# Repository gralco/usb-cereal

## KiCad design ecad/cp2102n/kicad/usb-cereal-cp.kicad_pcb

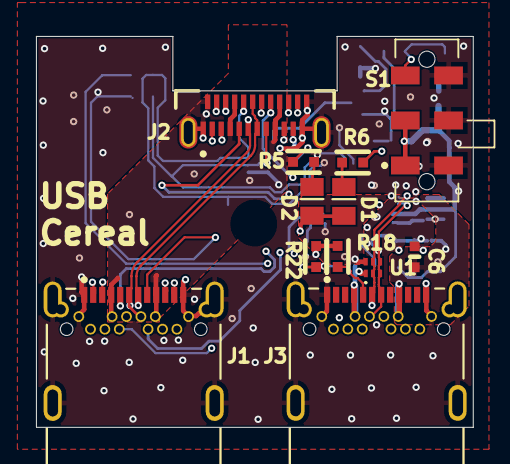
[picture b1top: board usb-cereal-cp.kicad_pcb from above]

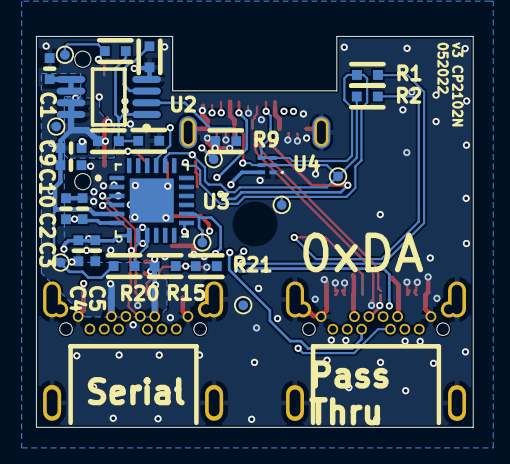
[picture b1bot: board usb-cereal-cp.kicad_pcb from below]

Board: 6 copper layers, 24.3 x 21.7 mm, 40 parts (28 on the bottom side), 35 nets.

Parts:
C1, C9, C10: 1µF; SMD-0402C
C2, C5: 0.10µF; SMD-0402C
C3, C4: 4.7µF; SMD-0402C
C6: 10nF; SMD-0402C
D1: LTST-C171GKT; 0805
D2: LTST-C171KSKT; 0805
J1, J3: UJ31-CH-G1-SMT-TR; CUI_UJ31-CH-G1-SMT-TR
J2: USB4155-03-C_REVA; GCT_USB4155-03-C_REVA
R1, R2, R16: 0.0; SMD-0402-RES
R5: 1k; SMD-0402-RES
R6: 270; SMD-0402-RES
R9, R10: 53.6k; SMD-0402-RES
R11, R15, R20: 22.1k; SMD-0402-RES
R12: 30.1k; SMD-0402-RES
R18, R22: 5.1k; SMD-0402-RES
R21: 47.5k; SMD-0402-RES
S1: JS202011JAQN
TP1, TP3, TP4, TP5, TP6, TP7, TP8, TP9: GND; Testpoint
U1, U4: ESDR0502NMUTAG; ONSC-UDFN-6-517AA-01_V
U2: TPS77401DGK; TI-DGK8_N
U3: CP2102N-A02-GQFN24R; QFN50P400X400X80-25N

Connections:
A5_CC1: J1.A5, J2.A5
A8_SBU1: J2.A8, R2.1, TP5.1, U3.20, U4.2, U4.5
B5_CC2: J1.B5, J2.B5
B8_SBU2: J2.B8, R1.1, TP3.1, U3.21, U4.3, U4.4
DBG_CC1: J3.A5, R18.2
DBG_CC2: J3.B5, R22.2
DBG_VBUS: C1.1, C4.1, C5.1, C6.1, J3.A4, J3.A9, J3.B4, J3.B9, R15.2, TP4.1, U1.6, U2.5, U2.6, U3.7
D_N: J1.A7, J1.B7, J2.A7, J2.B7
D_P: J1.A6, J1.B6, J2.A6, J2.B6
GND: C1.2, C2.2, C3.2, C4.2, C5.2, C6.2, C9.2, C10.2, J1.A1, J1.A12, J1.B1, J1.B12, J1.SH1, J1.SH2, J1.SH3, J1.SH4, J1.SH5, J1.SH6, J2.A1, J2.A12, J2.B1, J2.B12, J2.S1, J2.S2, J3.A1, J3.A12, J3.B1, J3.B12, J3.SH1, J3.SH2, J3.SH3, J3.SH4, J3.SH5, J3.SH6, R12.1, R16.1, R18.1, R21.1, R22.1, S1.4, S1.5, S1.6, U1.1, U2.4, U3.2, U3.25, U4.1
LDO_FB: R10.1, R11.1, R12.2, U2.1
NetD1_2: D1.2, R6.2
NetD2_2: D2.2, R5.2
NetR9_1: R9.1, U2.2
NetR11_2: R11.2, S1.3, TP8.1
NetR15_1: R15.1, R21.2, U3.8
NetR16_2: R16.2, U2.3
NetR20_1: R20.1, U3.9
RX1_N: J1.B10, J2.B10
RX1_P: J1.B11, J2.B11
RX2_N: J1.A10, J2.A10
RX2_P: J1.A11, J2.A11
RXLED: R5.1, TP9.1, U3.13
SBU1_R: J1.A8, R2.2
SBU2_R: J1.B8, R1.2
TX1_N: J1.A3, J2.A3
TX1_P: J1.A2, J2.A2
TX2_N: J1.B3, J2.B3
TX2_P: J1.B2, J2.B2
TXLED: R6.1, TP7.1, U3.14
USB_FT_HS_N: J3.A7, J3.B7, U1.3, U1.4, U3.4
USB_FT_HS_P: J3.A6, J3.B6, U1.2, U1.5, U3.3
VBUS: J1.A4, J1.A9, J1.B4, J1.B9, J2.A4, J2.A9, J2.B4, J2.B9, U4.6
VREG_OUT: C2.1, C3.1, D1.1, D2.1, U3.6
VSBU: C9.1, C10.1, R9.2, R10.2, R20.2, S1.1, S1.2, TP6.1, U2.7, U2.8, U3.5

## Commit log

2023-10-02 Convert the CP2102N variant of the board to KiCad
